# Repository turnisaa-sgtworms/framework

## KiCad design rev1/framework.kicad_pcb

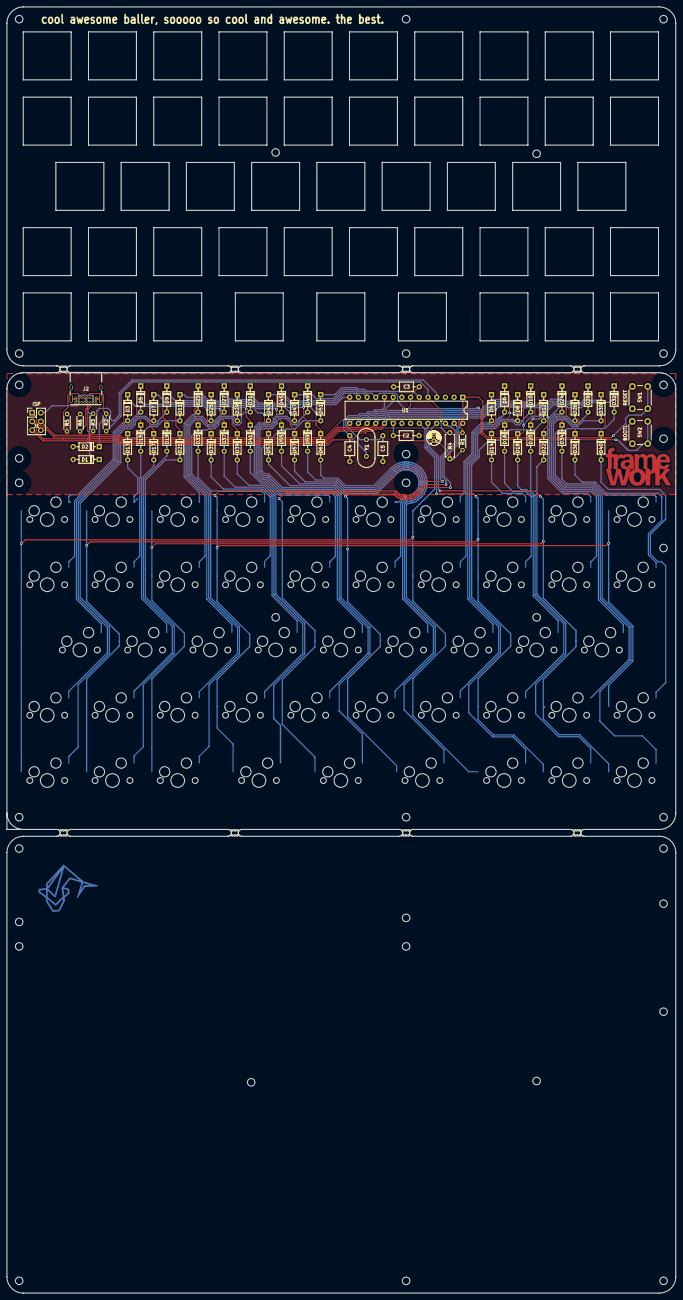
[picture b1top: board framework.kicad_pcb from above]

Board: 2 copper layers, 195.3 x 375.5 mm, 123 parts (0 on the bottom side), 25 nets.

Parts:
C1: 4u7; CP_Radial_D4.0mm_P1.50mm
C2, C3: 0u1; C_Axial_L3.8mm_D2.6mm_P7.50mm_Horizontal
C4, C5: 22p; C_Axial_L3.8mm_D2.6mm_P7.50mm_Horizontal
D1, D2: 3v6; D_DO-35_SOD27_P7.62mm_Horizontal
D3, D4, D5, D6, D7, D8, D9, D10, D11, D12, D13, D14, D15, D16, D17, D18, D19, D20, D21, D22, D23, D24, D25, D26, D27, D28, D29, D30, D31, D32, D33, D34, D35, D36, D37, D39, D40, D41, D43, D45, D47, D49, D51, D53, D55, D57, D59, D61: D; D_DO-35_SOD27_P7.62mm_Horizontal
J1: AVR-ISP-6; PinHeader_2x03_P2.54mm_Vertical
J2: USB_C_Receptacle_USB2.0; USB_C_Receptacle_GCT_USB4085
R1: 10k; R_Axial_DIN0204_L3.6mm_D1.6mm_P5.08mm_Horizontal
R2, R3: 75; R_Axial_DIN0204_L3.6mm_D1.6mm_P5.08mm_Horizontal
R4: 1k5; R_Axial_DIN0207_L6.3mm_D2.5mm_P7.62mm_Horizontal
R5, R6: 5k1; R_Axial_DIN0204_L3.6mm_D1.6mm_P5.08mm_Horizontal
SW1, SW2: SW_Push; SW_PUSH_6mm_H4.3mm
SW3, SW4, SW5, SW6, SW7, SW8, SW9, SW10, SW11, SW12, SW13, SW14, SW15, SW16, SW17, SW18, SW19, SW20, SW21, SW22, SW23, SW24, SW25, SW26, SW27, SW28, SW29, SW30, SW31, SW32, SW33, SW34, SW35, SW36, SW37, SW39, SW40, SW41, SW43, SW45, SW47, SW49, SW51, SW53, SW54, SW56, SW58, SW60: SW_Push_45deg; Kailh_socket_MX_no_fsilk
U1: ATmega328P-PU; DIP-28_W7.62mm
Y1: 16M; Crystal_HC49-4H_Vertical
mouse-bite-2mm-slot, mouse-bite-2mm-slot#2, mouse-bite-2mm-slot#3, mouse-bite-2mm-slot#4, mouse-bite-2mm-slot#5, mouse-bite-2mm-slot#6, mouse-bite-2mm-slot#7, mouse-bite-2mm-slot#8: VAL**; mouse-bite-2mm-slot

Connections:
+5V: C1.1, C2.1, C3.1, J1.2 (VCC), J2.A4 (VBUS), J2.A9 (VBUS), J2.B4 (VBUS), J2.B9 (VBUS), R1.1, R4.2, U1.7 (VCC), U1.20 (AVCC)
GND: C1.2, C2.2, C3.2, C4.2, C5.2, D1.2 (A), D2.2 (A), J1.6 (GND), J2.A1 (GND), J2.A12 (GND), J2.B1 (GND), J2.B12 (GND), J2.S1 (SHIELD), R5.1, R6.1, SW1.2, SW2.2, U1.8 (GND), U1.22 (GND)
unnamed: J2.A6 (D+), J2.B6 (D+), R3.2
unnamed: J2.A7 (D-), J2.B7 (D-), R2.2
unnamed: U1.9 (XTAL1/PB6), Y1.2
unnamed: U1.10 (XTAL2/PB7), Y1.1
c0: SW3.2, SW4.2, SW5.2, SW6.2, SW7.2, SW8.2, SW9.2, SW10.2, SW11.2, SW12.2, U1.23 (PC0)
c1: SW13.2, SW14.2, SW15.2, SW16.2, SW17.2, SW18.2, SW19.2, SW20.2, SW21.2, SW22.2, U1.24 (PC1)
c2: SW23.2, SW24.2, SW25.2, SW26.2, SW27.2, SW28.2, SW29.2, SW30.2, SW31.2, SW32.2, U1.25 (PC2)
c3: SW33.2, SW34.2, SW35.2, SW36.2, SW37.2, SW39.2, SW40.2, SW41.2, U1.26 (PC3)
c4: SW43.2, SW45.2, SW47.2, SW49.2, SW51.2, U1.27 (PC4)
c5: SW53.2, SW54.2, SW56.2, SW58.2, SW60.2, U1.28 (PC5)
d+: R3.1, U1.4 (PD2)
d-: R2.1, R4.1, U1.5 (PD3)
miso: D10.1 (K), D20.1 (K), D30.1 (K), D40.1 (K), J1.1 (MISO), U1.18 (PB4)
mosi: D8.1 (K), D18.1 (K), D28.1 (K), J1.4 (MOSI), U1.17 (PB3)
r0: D3.1 (K), D13.1 (K), D23.1 (K), D33.1 (K), D43.1 (K), D53.1 (K), U1.14 (PB0)
r1: D4.1 (K), D14.1 (K), D24.1 (K), D34.1 (K), U1.15 (PB1)
r2: D5.1 (K), D15.1 (K), D25.1 (K), D35.1 (K), D45.1 (K), D55.1 (K), U1.13 (PD7)
r3: D6.1 (K), D16.1 (K), D26.1 (K), D36.1 (K), U1.16 (PB2)
r4: D7.1 (K), D17.1 (K), D27.1 (K), D37.1 (K), D47.1 (K), D57.1 (K), U1.12 (PD6)
r6: D9.1 (K), D19.1 (K), D29.1 (K), D39.1 (K), D49.1 (K), D59.1 (K), SW2.1, U1.11 (PD5)
r8: D11.1 (K), D21.1 (K), D31.1 (K), D41.1 (K), D51.1 (K), D61.1 (K), U1.6 (PD4)
r9: D12.1 (K), D22.1 (K), D32.1 (K), J1.3 (SCK), U1.19 (PB5)
rst: J1.5 (~RST), R1.2, SW1.1, U1.1 (~RESET/PC6)

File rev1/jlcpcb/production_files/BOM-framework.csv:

Comment,Designator,Footprint,LCSC,Quantity
USB_C_Receptacle_USB2.0,J2,USB_C_Receptacle_GCT_USB4085,,1
1k5,R4,R_Axial_DIN0207_L6.3mm_D2.5mm_P7.62mm_Horizontal,,1
D,D33,D_DO-35_SOD27_P7.62mm_Horizontal,,1
5k1,R5,R_Axial_DIN0204_L3.6mm_D1.6mm_P5.08mm_Horizontal,,1
D,D53,D_DO-35_SOD27_P7.62mm_Horizontal,,1
D,D61,D_DO-35_SOD27_P7.62mm_Horizontal,,1
0u1,C2,C_Axial_L3.8mm_D2.6mm_P7.50mm_Horizontal,,1
SW_Push_45deg,SW6,Kailh_socket_MX_no_fsilk,,1
SW_Push_45deg,SW31,Kailh_socket_MX_no_fsilk,,1
SW_Push_45deg,SW24,Kailh_socket_MX_no_fsilk,,1
SW_Push_45deg,SW3,Kailh_socket_MX_no_fsilk,,1
SW_Push_45deg,SW33,Kailh_socket_MX_no_fsilk,,1
SW_Push_45deg,SW14,Kailh_socket_MX_no_fsilk,,1
SW_Push_45deg,SW17,Kailh_socket_MX_no_fsilk,,1
SW_Push_45deg,SW30,Kailh_socket_MX_no_fsilk,,1
SW_Push_45deg,SW22,Kailh_socket_MX_no_fsilk,,1
SW_Push_45deg,SW26,Kailh_socket_MX_no_fsilk,,1
SW_Push_45deg,SW27,Kailh_socket_MX_no_fsilk,,1
SW_Push_45deg,SW32,Kailh_socket_MX_no_fsilk,,1
SW_Push_45deg,SW43,Kailh_socket_MX_no_fsilk,,1
SW_Push_45deg,SW54,Kailh_socket_MX_no_fsilk,,1
SW_Push_45deg,SW45,Kailh_socket_MX_no_fsilk,,1
SW_Push_45deg,SW51,Kailh_socket_MX_no_fsilk,,1
SW_Push_45deg,SW35,Kailh_socket_MX_no_fsilk,,1
SW_Push_45deg,SW21,Kailh_socket_MX_no_fsilk,,1
SW_Push_45deg,SW9,Kailh_socket_MX_no_fsilk,,1
SW_Push_45deg,SW4,Kailh_socket_MX_no_fsilk,,1
SW_Push_45deg,SW12,Kailh_socket_MX_no_fsilk,,1
SW_Push_45deg,SW15,Kailh_socket_MX_no_fsilk,,1
SW_Push_45deg,SW20,Kailh_socket_MX_no_fsilk,,1
SW_Push_45deg,SW41,Kailh_socket_MX_no_fsilk,,1
ATmega328P-PU,U1,DIP-28_W7.62mm,,1
SW_Push_45deg,SW10,Kailh_socket_MX_no_fsilk,,1
SW_Push_45deg,SW5,Kailh_socket_MX_no_fsilk,,1
SW_Push_45deg,SW36,Kailh_socket_MX_no_fsilk,,1
D,D28,D_DO-35_SOD27_P7.62mm_Horizontal,,1
D,D21,D_DO-35_SOD27_P7.62mm_Horizontal,,1
D,D32,D_DO-35_SOD27_P7.62mm_Horizontal,,1
D,D31,D_DO-35_SOD27_P7.62mm_Horizontal,,1
D,D20,D_DO-35_SOD27_P7.62mm_Horizontal,,1
D,D55,D_DO-35_SOD27_P7.62mm_Horizontal,,1
D,D16,D_DO-35_SOD27_P7.62mm_Horizontal,,1
D,D30,D_DO-35_SOD27_P7.62mm_Horizontal,,1
D,D45,D_DO-35_SOD27_P7.62mm_Horizontal,,1
D,D22,D_DO-35_SOD27_P7.62mm_Horizontal,,1
D,D25,D_DO-35_SOD27_P7.62mm_Horizontal,,1
D,D26,D_DO-35_SOD27_P7.62mm_Horizontal,,1
D,D29,D_DO-35_SOD27_P7.62mm_Horizontal,,1
SW_Push_45deg,SW28,Kailh_socket_MX_no_fsilk,,1
D,D40,D_DO-35_SOD27_P7.62mm_Horizontal,,1
D,D39,D_DO-35_SOD27_P7.62mm_Horizontal,,1
D,D47,D_DO-35_SOD27_P7.62mm_Horizontal,,1
D,D17,D_DO-35_SOD27_P7.62mm_Horizontal,,1
D,D5,D_DO-35_SOD27_P7.62mm_Horizontal,,1
SW_Push_45deg,SW7,Kailh_socket_MX_no_fsilk,,1
22p,C4,C_Axial_L3.8mm_D2.6mm_P7.50mm_Horizontal,,1
D,D9,D_DO-35_SOD27_P7.62mm_Horizontal,,1
D,D4,D_DO-35_SOD27_P7.62mm_Horizontal,,1
D,D10,D_DO-35_SOD27_P7.62mm_Horizontal,,1
75,R2,R_Axial_DIN0204_L3.6mm_D1.6mm_P5.08mm_Horizontal,,1
10k,R1,R_Axial_DIN0204_L3.6mm_D1.6mm_P5.08mm_Horizontal,,1
D,D23,D_DO-35_SOD27_P7.62mm_Horizontal,,1
SW_Push_45deg,SW19,Kailh_socket_MX_no_fsilk,,1
D,D51,D_DO-35_SOD27_P7.62mm_Horizontal,,1
SW_Push_45deg,SW34,Kailh_socket_MX_no_fsilk,,1
AVR-ISP-6,J1,PinHeader_2x03_P2.54mm_Vertical,,1
SW_Push_45deg,SW18,Kailh_socket_MX_no_fsilk,,1
D,D34,D_DO-35_SOD27_P7.62mm_Horizontal,,1
SW_Push_45deg,SW23,Kailh_socket_MX_no_fsilk,,1
SW_Push_45deg,SW47,Kailh_socket_MX_no_fsilk,,1
D,D6,D_DO-35_SOD27_P7.62mm_Horizontal,,1
4u7,C1,CP_Radial_D4.0mm_P1.50mm,,1
D,D43,D_DO-35_SOD27_P7.62mm_Horizontal,,1
D,D14,D_DO-35_SOD27_P7.62mm_Horizontal,,1
SW_Push_45deg,SW53,Kailh_socket_MX_no_fsilk,,1
SW_Push_45deg,SW11,Kailh_socket_MX_no_fsilk,,1
SW_Push_45deg,SW49,Kailh_socket_MX_no_fsilk,,1
D,D19,D_DO-35_SOD27_P7.62mm_Horizontal,,1
SW_Push_45deg,SW8,Kailh_socket_MX_no_fsilk,,1
SW_Push_45deg,SW13,Kailh_socket_MX_no_fsilk,,1
3v6,D2,D_DO-35_SOD27_P7.62mm_Horizontal,,1
SW_Push_45deg,SW37,Kailh_socket_MX_no_fsilk,,1
SW_Push_45deg,SW60,Kailh_socket_MX_no_fsilk,,1
D,D36,D_DO-35_SOD27_P7.62mm_Horizontal,,1
D,D49,D_DO-35_SOD27_P7.62mm_Horizontal,,1
D,D15,D_DO-35_SOD27_P7.62mm_Horizontal,,1
SW_Push_45deg,SW29,Kailh_socket_MX_no_fsilk,,1
SW_Push_45deg,SW16,Kailh_socket_MX_no_fsilk,,1
D,D18,D_DO-35_SOD27_P7.62mm_Horizontal,,1
D,D41,D_DO-35_SOD27_P7.62mm_Horizontal,,1
D,D57,D_DO-35_SOD27_P7.62mm_Horizontal,,1
5k1,R6,R_Axial_DIN0204_L3.6mm_D1.6mm_P5.08mm_Horizontal,,1
D,D3,D_DO-35_SOD27_P7.62mm_Horizontal,,1
SW_Push_45deg,SW40,Kailh_socket_MX_no_fsilk,,1
SW_Push_45deg,SW25,Kailh_socket_MX_no_fsilk,,1
SW_Push,SW1,SW_PUSH_6mm_H4.3mm,,1
SW_Push_45deg,SW39,Kailh_socket_MX_no_fsilk,,1
D,D11,D_DO-35_SOD27_P7.62mm_Horizontal,,1
D,D24,D_DO-35_SOD27_P7.62mm_Horizontal,,1
D,D59,D_DO-35_SOD27_P7.62mm_Horizontal,,1
D,D37,D_DO-35_SOD27_P7.62mm_Horizontal,,1
0u1,C3,C_Axial_L3.8mm_D2.6mm_P7.50mm_Horizontal,,1
SW_Push_45deg,SW56,Kailh_socket_MX_no_fsilk,,1
3v6,D1,D_DO-35_SOD27_P7.62mm_Horizontal,,1
SW_Push,SW2,SW_PUSH_6mm_H4.3mm,,1
D,D35,D_DO-35_SOD27_P7.62mm_Horizontal,,1
SW_Push_45deg,SW58,Kailh_socket_MX_no_fsilk,,1
D,D13,D_DO-35_SOD27_P7.62mm_Horizontal,,1
75,R3,R_Axial_DIN0204_L3.6mm_D1.6mm_P5.08mm_Horizontal,,1
16M,Y1,Crystal_HC49-4H_Vertical,,1
22p,C5,C_Axial_L3.8mm_D2.6mm_P7.50mm_Horizontal,,1
D,D8,D_DO-35_SOD27_P7.62mm_Horizontal,,1
D,D12,D_DO-35_SOD27_P7.62mm_Horizontal,,1
D,D7,D_DO-35_SOD27_P7.62mm_Horizontal,,1
D,D27,D_DO-35_SOD27_P7.62mm_Horizontal,,1

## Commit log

2024-11-17 reformatted to 48 key iso-ish thing
2024-11-18 Finished? pcb, sch, bom, and pos
